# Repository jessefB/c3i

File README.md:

# c3i
Composite to CSI2 Camera Interface (aka CCCI aka c3i)

### Purpose
Add a readily-available composite video camera (sold as 'backup cameras') to Raspberry Pi over a MIPI CSI2 camera interface

### Basic function
The ADV7280-M chip does all the magic, automatically detecting the composite video format (NTSC or PAL) and converting that to YCrCb 4:2:2 video stream. The -M variant of this chip adds a MIPI CSI2 conversion block, providing a single lane output MIPI data stream. Raspberry Pi's have dual lane MIPI channels, but according to [this](https://forums.raspberrypi.com/viewtopic.php?p=1717572&sid=e0199da8a1beeaa71a4631e8f8f0ca87#p1717572) thread, using lane 0 alone will work. The ADV7280-M has 8 composite video inputs, selectable by writing over i2c to the input selector register. Other than a couple voltage regulators and passive components, I designed this interface nearly identical to the recommended/typical use shown in the [datasheet](https://www.analog.com/media/en/technical-documentation/data-sheets/ADV7280.PDF). 

Parts can be found at [Digikey](https://www.digikey.com/en/mylists/list/8FBMX8EIKW). At the time of writing, this cost me just shy of $20 before shipping in parts. With 

## ** Currently under development ** 
I haven't gotten this working yet. Still in early stages of development.

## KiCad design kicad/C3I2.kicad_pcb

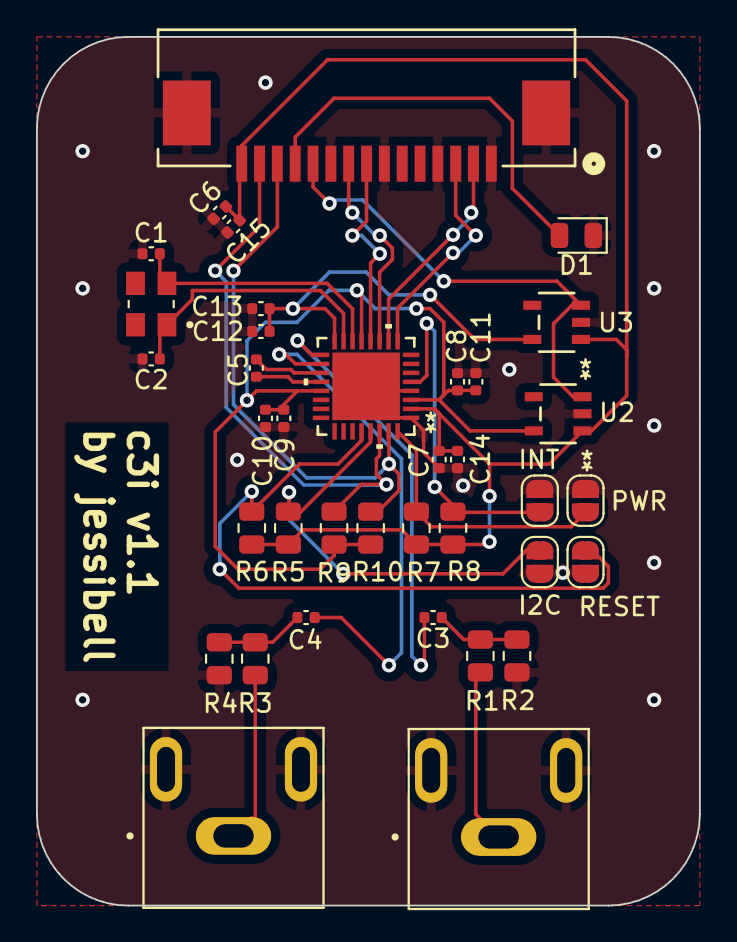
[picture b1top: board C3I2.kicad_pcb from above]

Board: 2 copper layers, 36.8 x 48.3 mm, 37 parts (0 on the bottom side), 26 nets.

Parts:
C1, C2: 47pF; C_0402_1005Metric
C3, C4, C5, C6, C8, C9, C12, C14, C15: 0.1uF; C_0402_1005Metric
C7, C10, C11, C13: 10nF; C_0402_1005Metric
D1: LED; LED_0805_2012Metric
I2C: Jumper_2_Open; SolderJumper-2_P1.3mm_Open_RoundedPad1.0x1.5mm
INT: Jumper_2_Open; SolderJumper-2_P1.3mm_Open_RoundedPad1.0x1.5mm
J1: 1-84952-5; conn15_1-84952-5_TEC
J2, J3: PJRAN1X1U04X; SWITCHCRAFT_PJRAN1X1U04X
PWR: Jumper_2_Open; SolderJumper-2_P1.3mm_Open_RoundedPad1.0x1.5mm
R1, R3: 24; R_0805_2012Metric
R2, R4: 51; R_0805_2012Metric
R5, R6, R7, R8: 100k; R_0805_2012Metric
R9, R10: 2.2k; R_0805_2012Metric
RESET: Jumper_2_Open; SolderJumper-2_P1.3mm_Open_RoundedPad1.0x1.5mm
U1: ADV7280BCPZ-M-RL; CP_32_12_ADI-M
U2, U3: MIC5504-1.8YM5-TR; SOT23-5LD-PL-1_MCH
Y1: 28.63636MHz; XTAL_ABM8-28.63636MHZ-B2-T

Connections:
+1V8: C8.2, C9.2, C10.2, C11.2, R9.1, R10.1, U1.3 (DVDD), U1.13 (MVDD), U1.21 (AVDD), U2.5 (VOUT)
+3.3V: C6.2, C7.2, C14.1, C15.1, J1.15, R5.1, R6.1, R7.1, R8.1, U1.2 (DVDDIO), U2.1 (VIN), U3.1 (VIN)
Ain1: C3.2, U1.17 (AIN1)
Ain2: C4.2, U1.18 (AIN2)
GND: C1.1, C2.1, C6.1, C7.1, C8.1, C9.1, C10.1, C11.1, C12.1, C13.1, C14.2, C15.2, D1.1 (K), I2C.1 (A), INT.1 (A), J1.1, J1.4, J1.7, J1.10, J1.16, J1.17, J2.2, J2.3, J3.2, J3.3, PWR.1 (A), R2.1, R4.1, RESET.1 (A), U1.1 (DGND), U1.4 (DGND), U1.33 (EPAD), U2.2 (GND), U3.2 (GND)
I2C_ADD: I2C.2 (B), R5.2, U1.29 (ALSB)
I2C_SCL: J1.13, R10.2, U1.31 (SCLK)
I2C_SDA: J1.14, R9.2, U1.30 (SDATA)
INT: INT.2 (B), R8.2, U1.5 (*INTRQ)
LED_IND: D1.2 (A), J1.12
MIPI_CL_N: J1.8, U1.12 (CLKN)
MIPI_CL_P: J1.9, U1.11 (CLKP)
MIPI_D0_N: J1.2, U1.10 (D0N)
MIPI_D0_P: J1.3, U1.9 (D0P)
unnamed: C3.1, R1.2, R2.2
unnamed: C4.1, R3.2, R4.2
unnamed: J2.1, R1.1
unnamed: J3.1, R3.1
unnamed: C5.2, U1.20 (VREFN)
unnamed: C5.1, U1.19 (VREFP)
unnamed: C2.2, U1.15 (XTALN), Y1.1
unnamed: C1.2, U1.14 (XTALP), Y1.2
PVDD: C12.2, C13.2, U1.16 (PVDD), U3.5 (VOUT)
PWRDWN: PWR.2 (B), R7.2, U1.32 (*PWRDWN)
PWR_EN: J1.11, U2.3 (EN), U3.3 (EN)
RESET: R6.2, RESET.2 (B), U1.28 (*RESET)

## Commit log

2023-12-06 organize
2023-12-06 gitignore
2023-12-06 readme
2023-12-06 Added image
2023-12-30 Revised PCB, issue 1
